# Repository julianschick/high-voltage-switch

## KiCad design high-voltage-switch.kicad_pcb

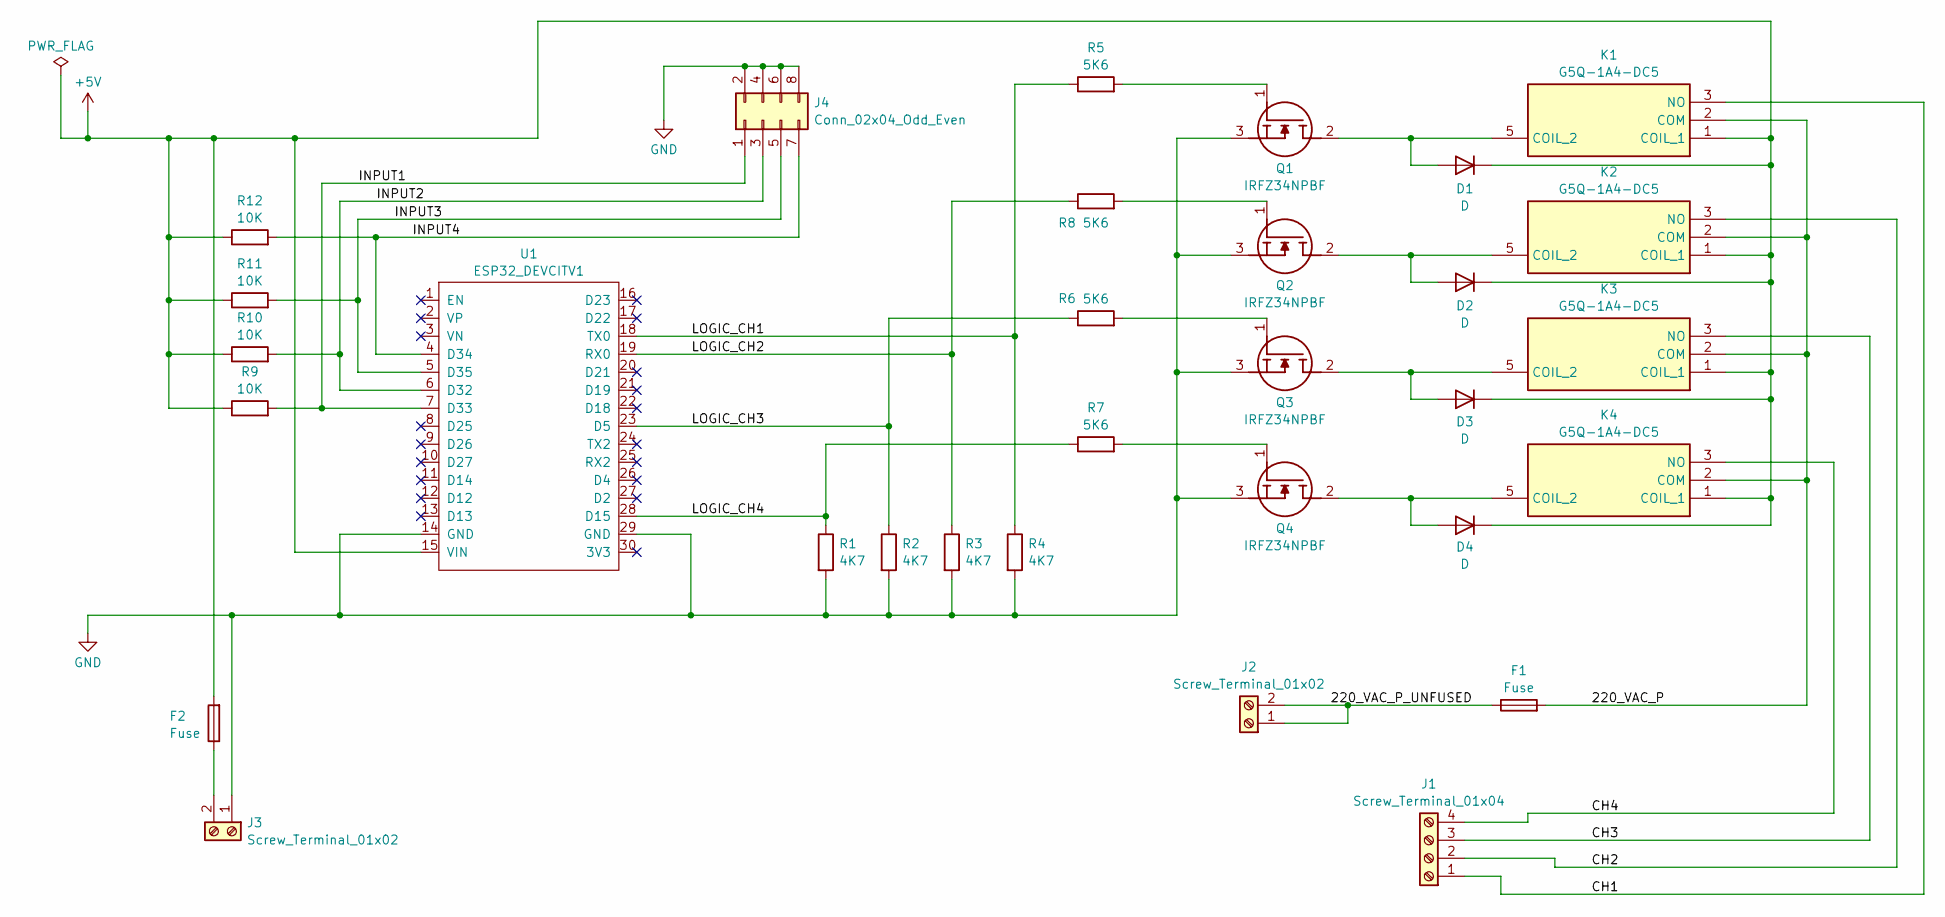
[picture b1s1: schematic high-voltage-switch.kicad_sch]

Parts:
D1, D2, D3, D4: D; D_DO-15_P12.70mm_Horizontal
F1, F2: Fuse; Fuseholder_Littelfuse_445_030_series_5x20mm
J1: Screw_Terminal_01x04; TB00475004GR
J2, J3: Screw_Terminal_01x02; TB00475002GR
J4: Conn_02x04_Odd_Even; PinHeader_2x04_P2.54mm_Vertical
K1, K2, K3, K4: G5Q-1A4-DC5; G5Q1A4DC5; Mouser Part Number 653-G5Q-1A4-DC5
Q1, Q2, Q3, Q4: IRFZ34NPBF; TO254P469X1042X1967-3P; Mouser Part Number 942-IRFZ34NPBF
R1, R2, R3, R4: 4K7; R_Axial_DIN0309_L9.0mm_D3.2mm_P12.70mm_Horizontal
R5, R6, R7, R8: 5K6; R_Axial_DIN0309_L9.0mm_D3.2mm_P12.70mm_Horizontal
R9, R10, R11, R12: 10K; R_Axial_DIN0309_L9.0mm_D3.2mm_P12.70mm_Horizontal
U1: ESP32_DEVCITV1; ESP32_DEVKITV1

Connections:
+5V: D1.1 (K), D2.1 (K), D3.1 (K), D4.1 (K), F2.2, K1.1 (COIL_1), K2.1 (COIL_1), K3.1 (COIL_1), K4.1 (COIL_1), R9.1, R10.1, R11.1, R12.1, U1.15 (VIN)
/220_VAC_P: F1.2, K1.2 (COM), K2.2 (COM), K3.2 (COM), K4.2 (COM)
/220_VAC_P_UNFUSED: F1.1, J2.1, J2.2
/CH1: J1.1, K1.3 (NO)
/CH2: J1.2, K2.3 (NO)
/CH3: J1.3, K3.3 (NO)
/CH4: J1.4, K4.3 (NO)
/INPUT1: J4.1, R9.2, U1.7 (D33)
/INPUT2: J4.3, R10.2, U1.6 (D32)
/INPUT3: J4.5, R11.2, U1.5 (D35)
/INPUT4: J4.7, R12.2, U1.4 (D34)
/LOGIC_CH1: R4.1, R5.1, U1.18 (TX0)
/LOGIC_CH2: R3.1, R8.1, U1.19 (RX0)
/LOGIC_CH3: R2.1, R6.1, U1.23 (D5)
/LOGIC_CH4: R1.1, R7.1, U1.28 (D15)
GND: J3.1, J4.2, J4.4, J4.6, J4.8, Q1.3 (S), Q2.3 (S), Q3.3 (S), Q4.3 (S), R1.2, R2.2, R3.2, R4.2, U1.14 (GND), U1.29 (GND)
unnamed: D1.2 (A), K1.5 (COIL_2), Q1.2 (D)
unnamed: D2.2 (A), K2.5 (COIL_2), Q2.2 (D)
unnamed: D3.2 (A), K3.5 (COIL_2), Q3.2 (D)
unnamed: D4.2 (A), K4.5 (COIL_2), Q4.2 (D)
unnamed: F2.1, J3.2
unnamed: Q1.1 (G), R5.2
unnamed: Q2.1 (G), R8.2
unnamed: Q3.1 (G), R6.2
unnamed: Q4.1 (G), R7.2

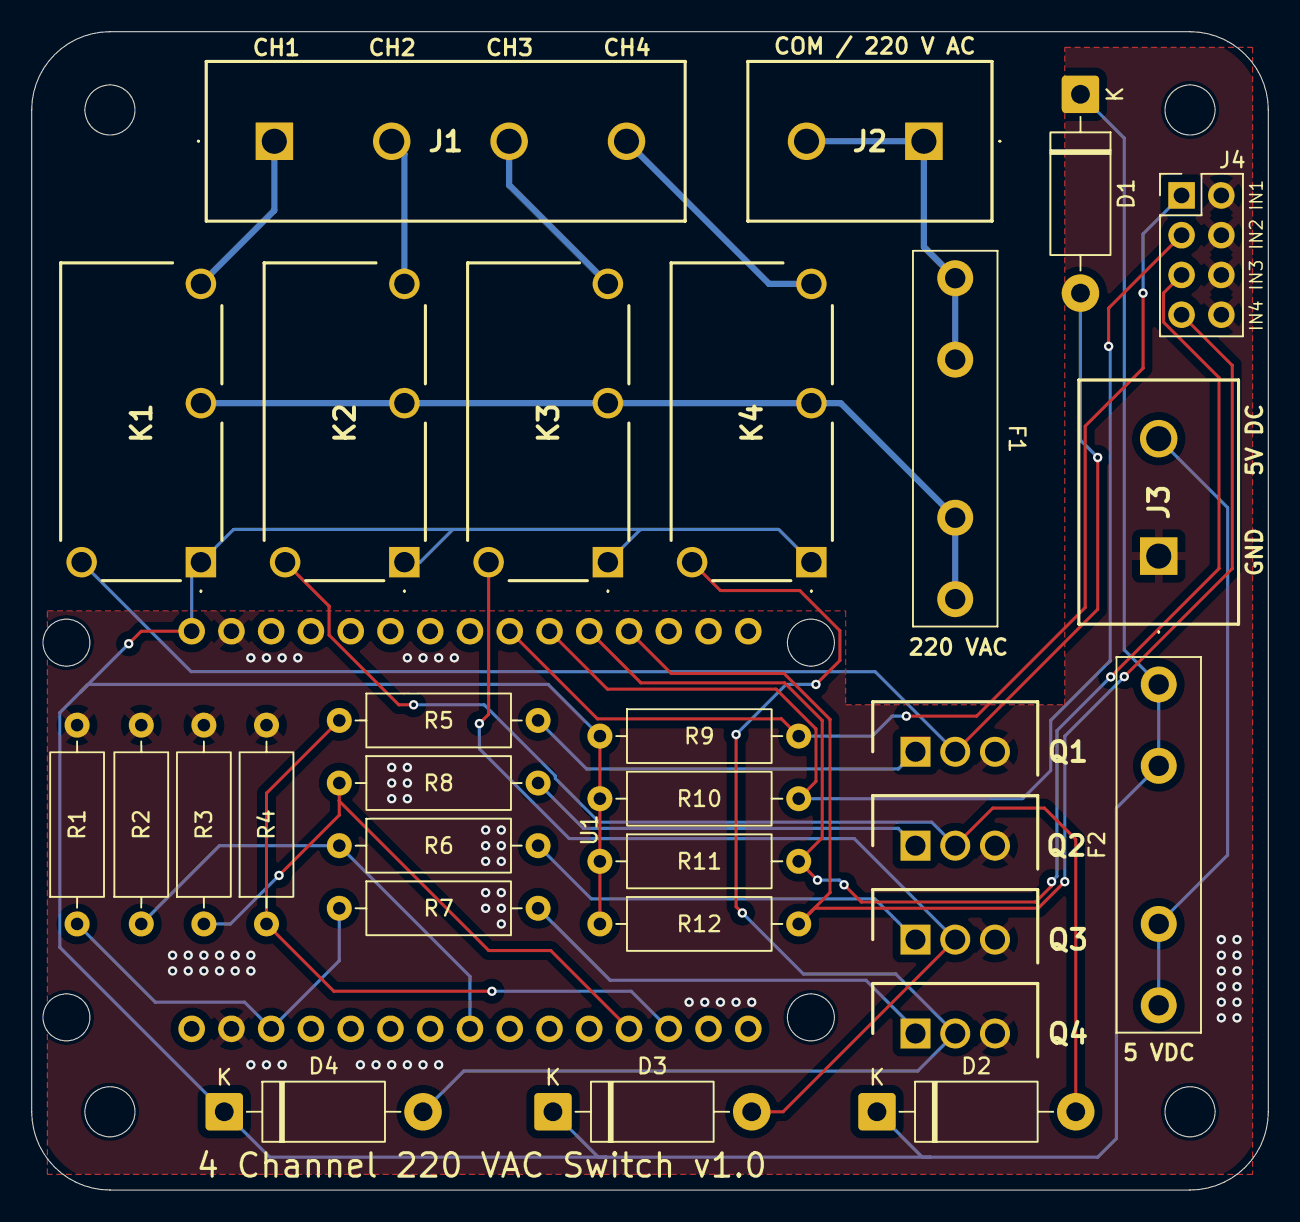
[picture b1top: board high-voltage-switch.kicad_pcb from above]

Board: 2 copper layers, 79.0 x 74.0 mm, 35 parts (0 on the bottom side), 25 nets.

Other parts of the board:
HOLE_NE: MountingHole_3.2mm_M3_DIN965
HOLE_NW: MountingHole_3.2mm_M3_DIN96; MountingHole_3.2mm_M3_DIN965
HOLE_SE: MountingHole_3.2mm_M3_DIN965
HOLE_SW: MountingHole_3.2mm_M3_DIN965

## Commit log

2025-07-08 initial
2025-07-08 add gitignore
2025-07-13 final version 1.0
